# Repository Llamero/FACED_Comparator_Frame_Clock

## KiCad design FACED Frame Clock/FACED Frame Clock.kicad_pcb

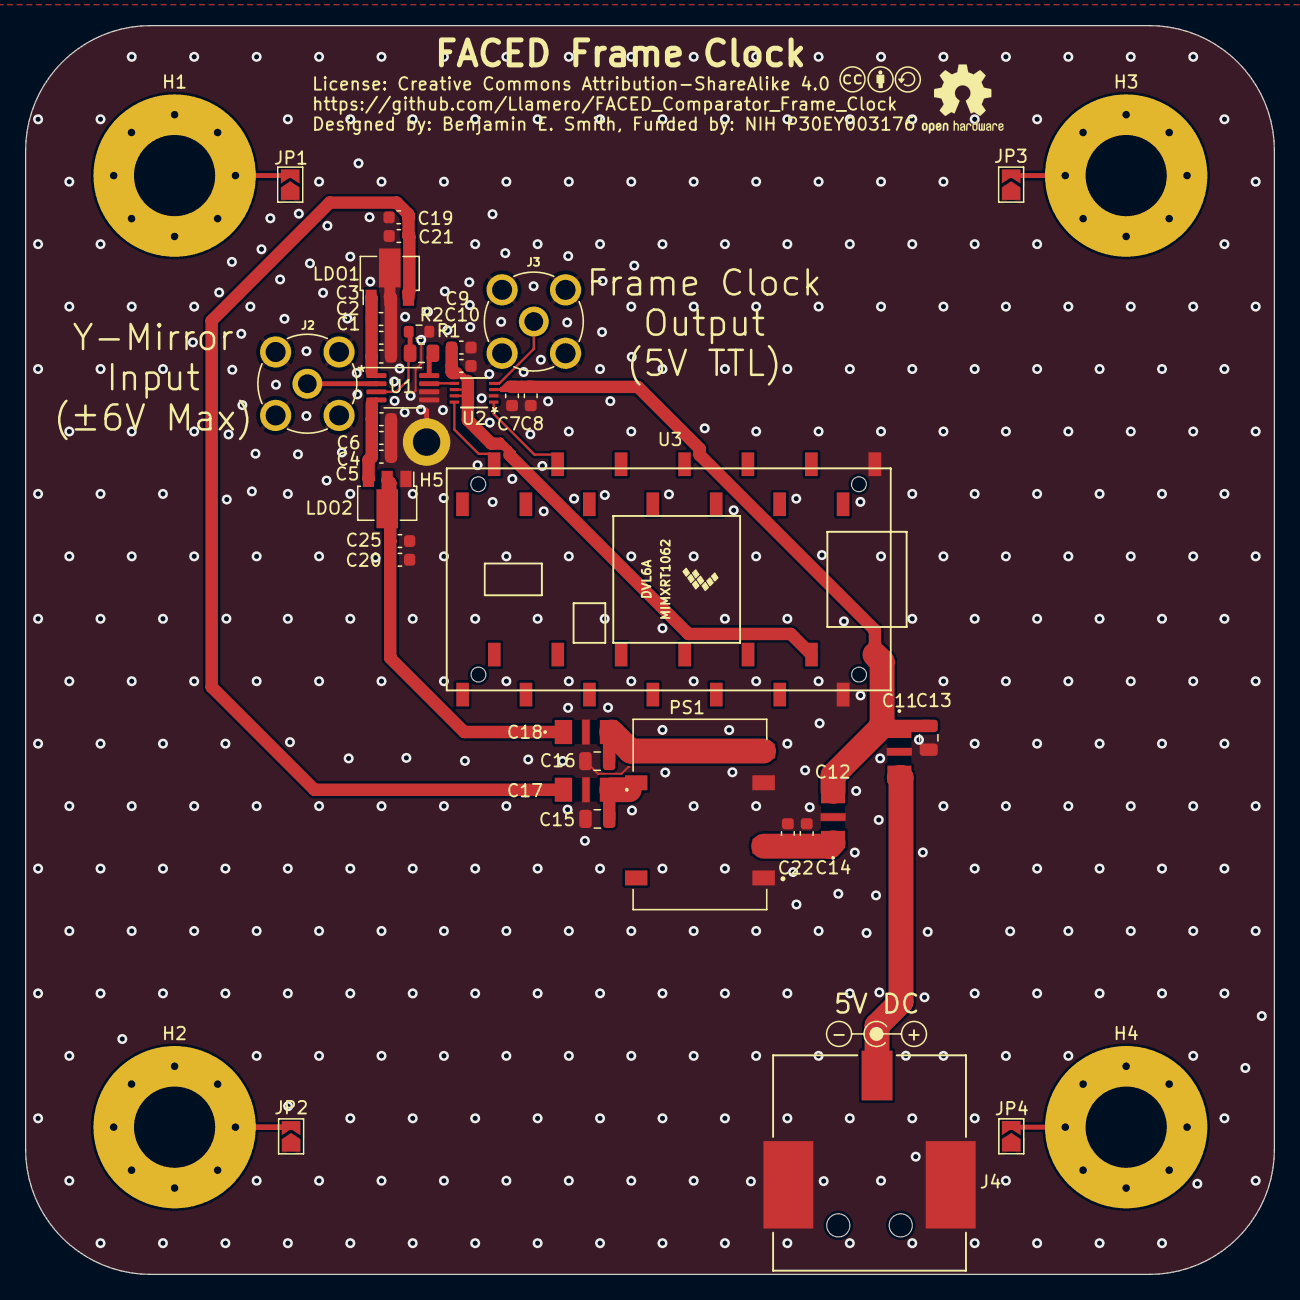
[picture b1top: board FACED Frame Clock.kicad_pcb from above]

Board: 2 copper layers, 100.0 x 100.0 mm, 46 parts (0 on the bottom side), 22 nets.

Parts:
C1, C6: 1nF; C_0603_1608Metric
C2, C4, C7, C9, C21, C22, C25: 0.1µF; C_0603_1608Metric
C3, C5, C8, C10, C14, C19, C20: 4.7µF; C_0603_1608Metric
C11, C12, C17, C18: ACH3218-103-TD01; CAP_TDK_ACH3218_TDK
C13, C15, C16: 22µF; C_0805_2012Metric
H1, H2, H3, H4: MountingHole_6.5mm_Pad_Via
H5: MountingHole_Pad; MountingHole_2.2mm_M2_DIN965_Pad
J2, J3: Conn_Coaxial; LINX_CONSMA001-C-G
J4: Barrel_Jack_Switch; Barrel_jack_694108105102_WRE
JP1, JP2, JP3, JP4: SolderJumper-2_P1.3mm_Open_TrianglePad1.0x1.5mm
LDO1: +6V LDO; SOT-89-3
LDO2: -6V LDO; SOT-89-3
LOGO1: CC license; Creative_commons_license
LOGO2: Jack Polarity; Polarity_Center_Positive
LOGO3: OSHW Logo; OSHW-Logo2_7.3x6mm_SilkScreen
PS1: R2D-0509; CONV_R2D-0509
R1: 47k; R_0805_2012Metric
R2: 47; R_0603_1608Metric
U1: LT1711xMS8; MSOP-8_3x3mm_P0.65mm
U2: TXU0202DCUR
U3: Teensy4.0; Teensy40-with headers

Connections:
+3V3: C9.2, C10.1, U2.6 (OE), U2.7 (VCCB), U3.31 (3V3)
+5V: C7.2, C8.1, C11.1, C12.3, C13.2, U2.3 (VCCA), U3.33 (VIN)
+6V: C1.2, C2.2, C3.1, LDO1.1 (Vout), U1.1 (V+)
-6V: C4.2, C5.1, C6.2, LDO2.3 (Vout), U1.4 (V-)
/9V: C15.1, C17.1, PS1.7 (+VOUT)
/-9V: C16.2, C18.3, PS1.5 (-VOUT)
/Frame_clock_3v3: U2.1 (B2), U3.11 (9_OUT1C)
/Frame_clock_5V: J3.1 (In), U2.4 (A2Y)
/Mirror_phase_3v3: U2.8 (B1Y), U3.13 (11_MOSI_CTX1)
/Mirror_phase_5v5: U1.7 (Q), U2.5 (A1)
/Vmirror: J2.1 (In), U1.2 (+)
/hysteresis: R1.2, R2.2, U1.3 (-)
GND: C1.1, C2.1, C3.2, C4.1, C5.2, C6.1, C7.1, C8.2, C9.1, C10.2, C11.2, C12.2, C13.1, C14.1, C15.2, C16.1, C17.2, C18.2, C19.1, C20.1, C21.1, C22.1, C25.1, H5.1, J2.2 (Ext), J3.2 (Ext), J4.2, J4.3, JP1.1 (A), JP2.1 (A), JP3.1 (A), JP4.1 (A), LDO1.2 (GND), LDO2.1 (GND), PS1.1 (-VIN), PS1.4 (COM), R2.1, U1.5 (LATCH), U1.6 (GND), U2.2 (GND), U3.1 (GND), U3.32 (GND)
unnamed: C11.3, J4.1
unnamed: H1.1, JP1.2 (B)
unnamed: H2.1, JP2.2 (B)
unnamed: H3.1, JP3.2 (B)
unnamed: H4.1, JP4.2 (B)
unnamed: C17.3, C19.2, C21.2, LDO1.3 (Vin)
unnamed: C18.1, C20.2, C25.2, LDO2.2 (Vin)
unnamed: C12.1, C14.2, C22.2, PS1.2 (+VIN)
unnamed: R1.1, U1.8 (~Q)

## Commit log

2024-09-05 Initial draft of schematic
2024-09-05 Label schematic
2024-09-05 Working draft of simplified version
2024-09-06 Rough draft of PCB
2024-09-06 move DC jack, more guard vias
2024-09-07 Revision submitted for order
2024-09-07 Improve grounding - thermal relief on mounting hole jumpers

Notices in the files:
FACED Frame Clock/FACED Frame Clock.kicad_pcb:
License: Creative Commons Attribution-ShareAlike 4.0
